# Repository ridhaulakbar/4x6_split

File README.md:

## 4x6 Split Ergo Keyboard

#### PCB:

* 4x6 matrix
* Designed to be flippable, same pcb for both sides
* No LED support

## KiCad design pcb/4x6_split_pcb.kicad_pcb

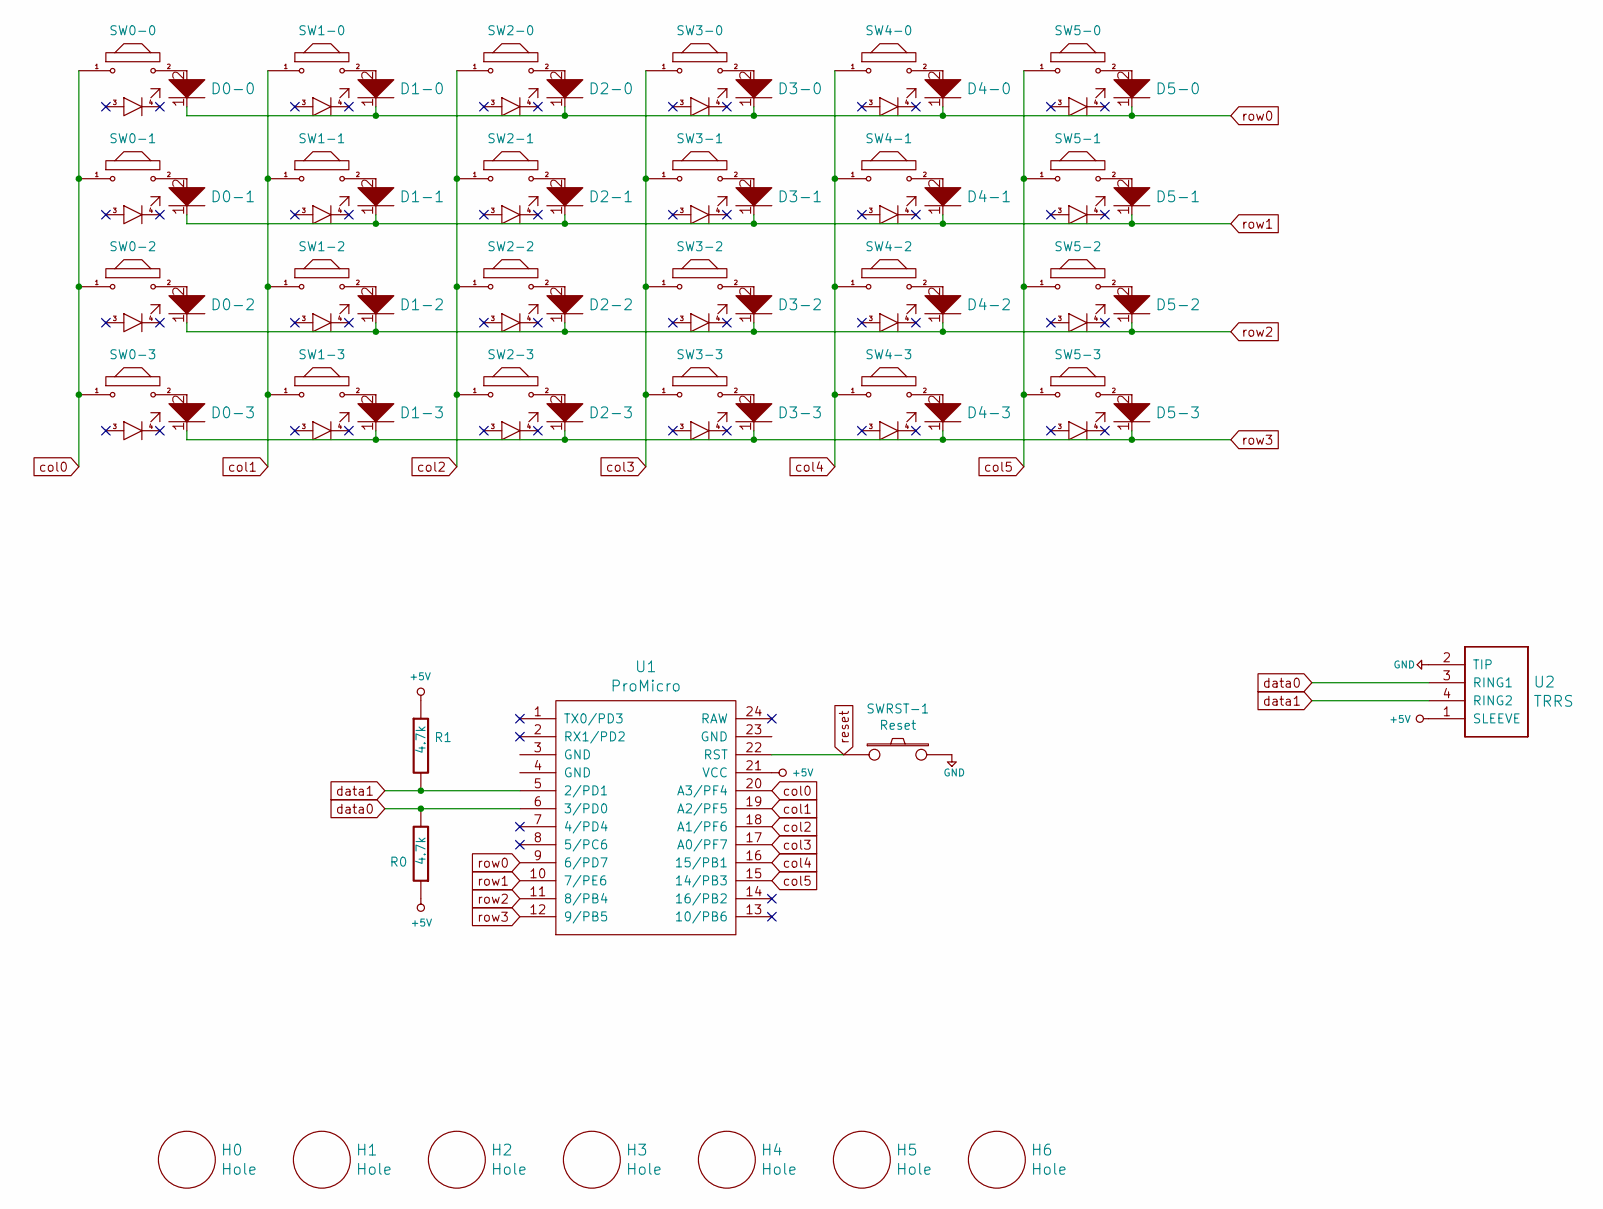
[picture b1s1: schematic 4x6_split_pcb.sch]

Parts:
D0-0, D0-1, D0-2, D0-3, D1-0, D1-1, D1-2, D1-3, D2-0, D2-1, D2-2, D2-3, D3-0, D3-1, D3-2, D3-3, D4-0, D4-1, D4-2, D4-3, D5-0, D5-1, D5-2, D5-3: D; Diode
H0, H1, H2, H3, H4, H5, H6: Hole; MountingHole
R0, R1: 4.7k; Resistor
SW0-0, SW0-1, SW0-2, SW0-3, SW1-0, SW1-1, SW1-2, SW1-3, SW2-0, SW2-1, SW2-2, SW2-3, SW3-0, SW3-1, SW3-2, SW3-3, SW4-0, SW4-1, SW4-2, SW4-3, SW5-0, SW5-1, SW5-2, SW5-3: MX; Triple-Dual-1u-LED
SWRST-1: Reset; SW_Tactile_SPST_Angled_MJTP1117
U1: ProMicro; ArduinoProMicro
U2: TRRS; TRRS-PJ-320A

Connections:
unnamed: D0-0.2, SW0-0.2
unnamed: D0-1.2, SW0-1.2
unnamed: D0-2.2, SW0-2.2
unnamed: D0-3.2, SW0-3.2
unnamed: D1-0.2, SW1-0.2
unnamed: D1-1.2, SW1-1.2
unnamed: D1-2.2, SW1-2.2
unnamed: D1-3.2, SW1-3.2
unnamed: D2-0.2, SW2-0.2
unnamed: D2-1.2, SW2-1.2
unnamed: D2-2.2, SW2-2.2
unnamed: D2-3.2, SW2-3.2
unnamed: D3-0.2, SW3-0.2
unnamed: D3-1.2, SW3-1.2
unnamed: D3-2.2, SW3-2.2
unnamed: D3-3.2, SW3-3.2
unnamed: D4-0.2, SW4-0.2
unnamed: D4-1.2, SW4-1.2
unnamed: D4-2.2, SW4-2.2
unnamed: D4-3.2, SW4-3.2
unnamed: D5-0.2, SW5-0.2
unnamed: D5-1.2, SW5-1.2
unnamed: D5-2.2, SW5-2.2
unnamed: D5-3.2, SW5-3.2
col0: SW0-0.1, SW0-1.1, SW0-2.1, SW0-3.1, U1.20 (A3/PF4)
col1: SW1-0.1, SW1-1.1, SW1-2.1, SW1-3.1, U1.19 (A2/PF5)
col2: SW2-0.1, SW2-1.1, SW2-2.1, SW2-3.1, U1.18 (A1/PF6)
col3: SW3-0.1, SW3-1.1, SW3-2.1, SW3-3.1, U1.17 (A0/PF7)
col4: SW4-0.1, SW4-1.1, SW4-2.1, SW4-3.1, U1.16 (15/PB1)
col5: SW5-0.1, SW5-1.1, SW5-2.1, SW5-3.1, U1.15 (14/PB3)
data0: R0.2, U1.6 (3/PD0), U2.3 (RING1)
data1: R1.2, U1.5 (2/PD1), U2.4 (RING2)
reset: SWRST-1.1, U1.22 (RST)
row0: D0-0.1, D1-0.1, D2-0.1, D3-0.1, D4-0.1, D5-0.1, U1.9 (6/PD7)
row1: D0-1.1, D1-1.1, D2-1.1, D3-1.1, D4-1.1, D5-1.1, U1.10 (7/PE6)
row2: D0-2.1, D1-2.1, D2-2.1, D3-2.1, D4-2.1, D5-2.1, U1.11 (8/PB4)
row3: D0-3.1, D1-3.1, D2-3.1, D3-3.1, D4-3.1, D5-3.1, U1.12 (9/PB5)

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
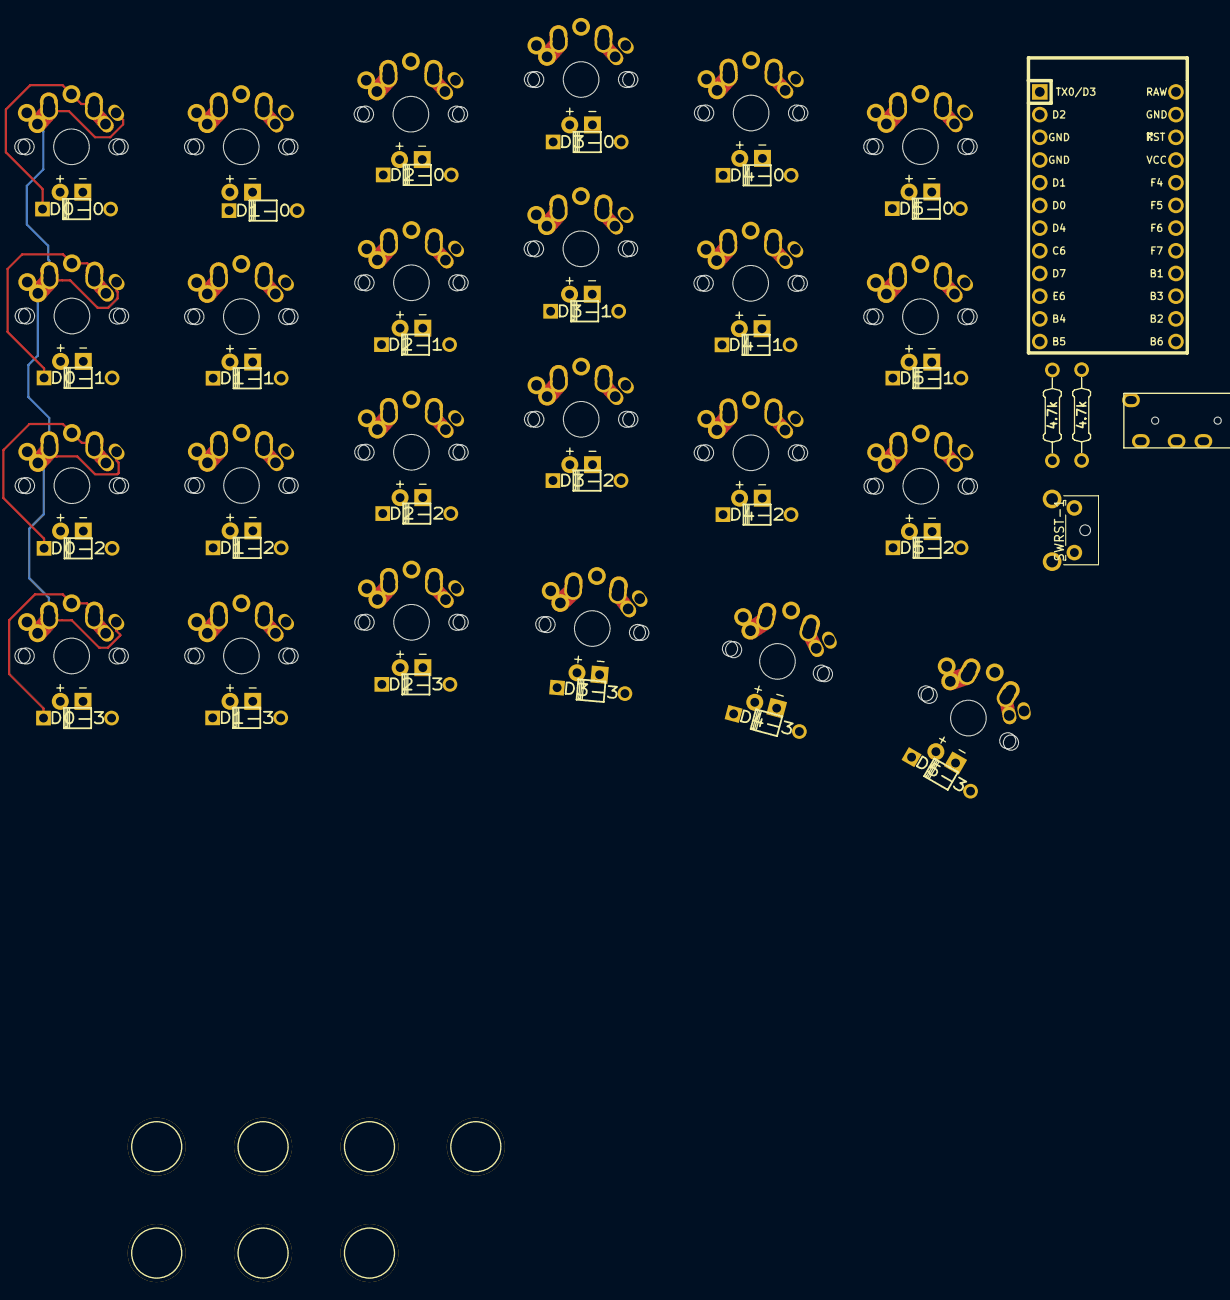
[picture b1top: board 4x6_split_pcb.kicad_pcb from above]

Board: 2 copper layers, 60 parts (0 on the bottom side), 38 nets.

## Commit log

2019-12-20 added plate and pcb template dxf
2019-12-20 added kicad files
2019-12-20 details on the pull request descriptions.
